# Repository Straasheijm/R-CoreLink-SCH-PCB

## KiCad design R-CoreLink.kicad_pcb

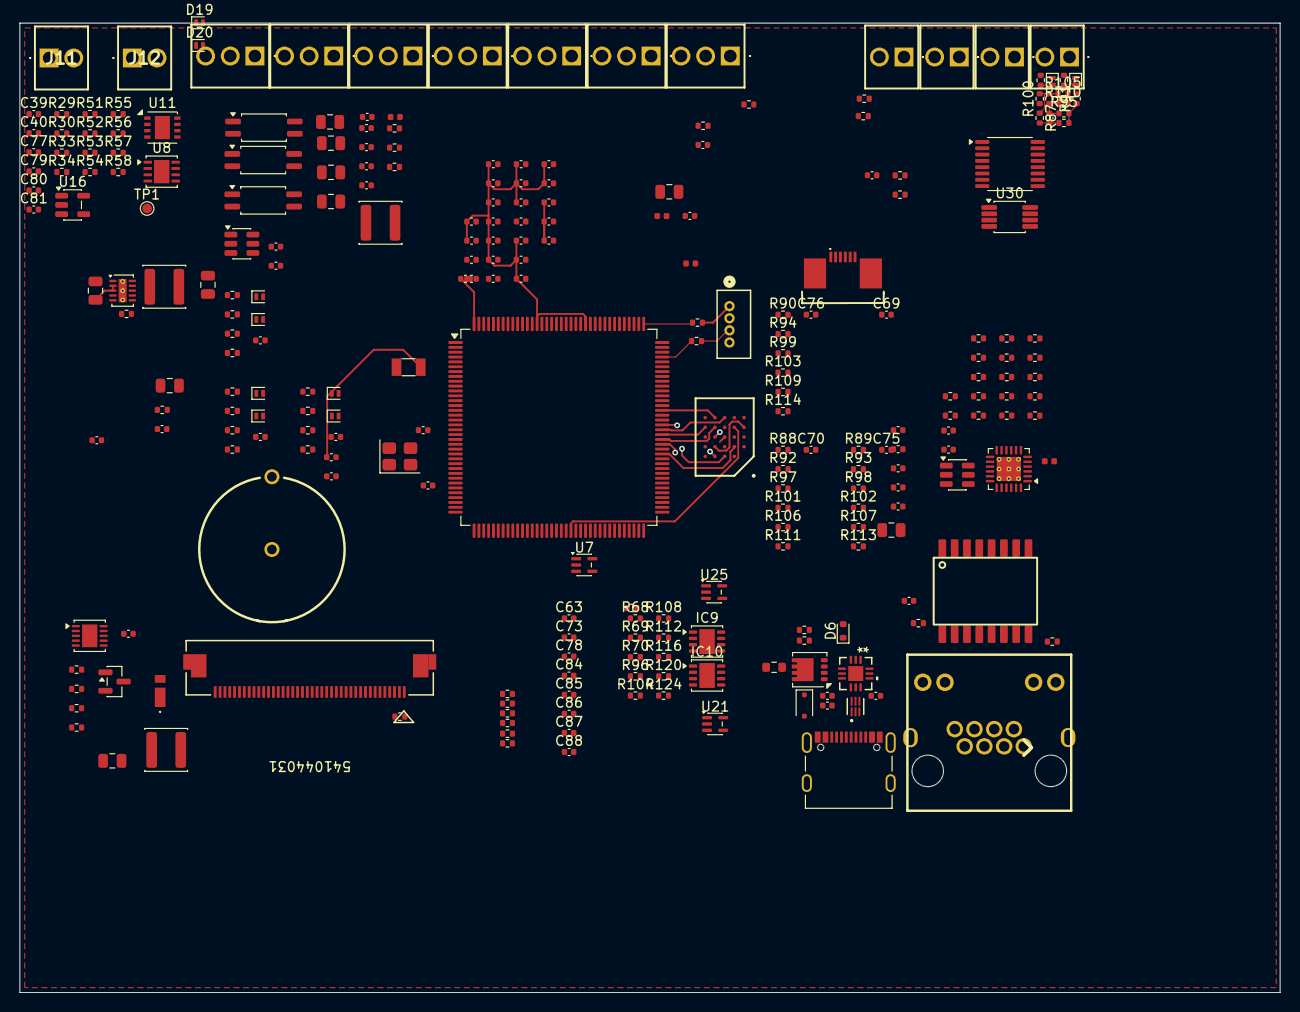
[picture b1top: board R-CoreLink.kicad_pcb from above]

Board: 4 copper layers, 130.0 x 100.0 mm, 260 parts (0 on the bottom side), 196 nets.

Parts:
BT1: Battery_Cell; CH23-1220LF
C1, C2, C4, C5, C7, C8, C9, C14, C15, C17, C18, C19, C20, C21, C22, C23, C24, C25, C32, C34, C36, C39, C40, C43, C47, C49, C51, C54, C56, C58, C63, C64, C65, C66, C67, C68, C71, C73, C74, C77, C78, C79, C80, C81, C83, C84, C85, C86, C87, C88: 100n; C_0402_1005Metric
C3: 1n; C_0402_1005Metric
C6, C10, C11, C26, C48, C50, C52, C53, C55, C62: 10u; C_0805_2012Metric
C12, C13, C41, C42: 15p; C_0402_1005Metric
C16, C28, C29: 4u7; C_0402_1005Metric
C27, C30, C31, C33, C35, C46, C57, C69, C70, C72, C75, C76: 1u; C_0402_1005Metric
C37, C38: 2u2; C_0402_1005Metric
C44, C45: 330p; C_0402_1005Metric
D2: ESD3Z24GW; D_SOD-323F
D6: RB530SM-40; D_SOD-523
D7: SDB160WS-AQ; SOD323HE
D11, D12, D13, D14, D15, D16, D17, D18, D19, D20: PESD3V3L1BSL; D_SOD-882
IC1: APS6408L-3OC-BA; BGA24C100P5X5_600X800X120
IC2: AL8866QFN-7; DFN-10-1EP_3x3mm_P0.5mm_EP1.58x2.35mm
IC9, IC10: MCP6n16-100E_MF; DFN-8-1EP_3x3mm_P0.65mm_EP1.6x2.56mm
J1: 541044031; CON_541044031_MOL
J2: RJHSE5384H1
J3, J5, J6, J7, J8, J9, J10: TBC05-03-1-G-G; TBC05031GG
J4: 10155435-00011LF; AMPHENOL_10155435-00011LF
J11, J12, J19, J20, J21, J22: TBC05-02-1-G-G; TBC05021GG
J13: 530470410; CONN04_530470410_MOL
J14: 1734839-6; 17348396
L1, L4, L7: MMZ1005A601ETD25; L_0402_1005Metric
L2, L3, L5: IFSC1515AHER100M01; L_Pulse_PA4332
Q1: DMG7430LFG; Diodes_PowerDI3333-8MOSFET
Q2: IRLML2060; SOT-23
R1, R9, R10, R11, R13, R21, R26, R36, R47, R51, R58, R70, R104, R112: 10K; R_0402_1005Metric
R2, R105, R106, R107, R109, R121, R122: 0; R_0402_1005Metric
R3, R4, R52, R53, R54, R55, R56, R57: 4K7; R_0402_1005Metric
R5, R6, R30, R37, R41, R44, R68, R69, R116, R120, R124: 100; R_0402_1005Metric
R7, R8: 75; R_0402_1005Metric
R12: 1K5; R_0402_1005Metric
R14, R16, R17, R18, R19, R20, R22, R23, R24, R28, R31, R32: 33; R_0402_1005Metric
R15, R25: 270; R_0402_1005Metric
R27: 330; R_0402_1005Metric
R29, R33, R34: 150; R_0402_1005Metric
R35: 2K4; R_0402_1005Metric
R38, R96, R108: 100K; R_0402_1005Metric
R39: 13K5; R_0402_1005Metric
R40: 47K; R_0402_1005Metric
R42: 12K1; R_0402_1005Metric
R45: 0; R_0603_1608Metric
R46: 250m; R_0402_1005Metric
R48: 270K; R_0402_1005Metric
R49: 10; R_0402_1005Metric
R71, R77, R81, R85, R95, R97, R98, R99, R100, R101, R102, R103: 5K; R_0402_1005Metric
R72, R78, R82, R86: 68; R_0402_1005Metric
R73, R74, R75, R76, R79, R80, R83, R84: 1K; R_0402_1005Metric
R87, R88, R89, R90, R110, R111, R113, R114: 22K; R_0402_1005Metric
R91, R92, R93, R94: 2K5; R_0402_1005Metric
STP1: STP1; L_0402_1005Metric
TH2: NTCG104BF473FT1X; R_0402_1005Metric
TP1: OP_OUT; TestPoint_Pad_D1.0mm
TR1: KMS-1102NL
U1: STM32H5E5ZJT6; LQFP-144_20x20mm_P0.5mm
U2: LAN8742A; VQFN-24-1EP_4x4mm_P0.5mm_EP2.5x2.5mm_ThermalVias
U3: USBLC6-4SC6; SOT-23-6
U4: TCPP01-M12; QFN12_TCPP01-M12_STM
U5: ECMF2-40A100N6; QFN6L_ECMF2_STM
U6: TPS62177DQC; WSON-10-1EP_2x3mm_P0.5mm_EP0.84x2.4mm_ThermalVias
U7: OPA333xxDCK; SOT-353_SC-70-5
U8: SN65HVD75DRBR; VSON-8-1EP_3x3mm_P0.65mm_EP1.6x2.4mm
U9: TPS561300DDCR; SOT-23-6
U11: NCV7344AMW3R2G; DFN-8-1EP_3x3mm_P0.65mm_EP1.55x2.4mm
U12, U13, U14: TCMT1100; SOP-4_4.4x2.6mm_P1.27mm
U15: TMUX1109PW; TSSOP-16_4.4x5mm_P0.65mm
U16: AP2171W; SOT-23-5
U21, U25: TLV9061xDCK; SOT-353_SC-70-5
U30: TMUX1121DGK; VSSOP-8_3x3mm_P0.65mm
Y1: XC32M4-24.000-F12NJDTL; Crystal_SMD_3225-4Pin_3.2x2.5mm
Y2: LFXTAL009678; Crystal_SMD_3215-2Pin_3.2x1.5mm

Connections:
+3.3V: C7.1, C11.1, C14.1, C15.1, C16.1, C17.1, C18.1, C19.1, C20.1, C21.1, C22.1, C23.1, C24.1, C25.1, C28.1, C29.1, C30.1, C31.1, C40.1, C57.1, C58.1, IC1.B4 (VDD), IC1.D1 (VDDQ_1), IC1.E4 (VDDQ_2), J1.4, J14.2, L1.1, L2.2, L4.2, R2.1, R3.1, R4.1, R9.1, R10.1, R11.1, R12.1, R13.1, R26.1, U1.17 (VDD), U1.30 (VDD), U1.39 (VDD), U1.52 (VDD), U1.62 (VDD), U1.72 (VDD), U1.84 (VDD), U1.94 (VDD), U1.106 (VDDSUSB), U1.108 (VDD), U1.121 (VDDIO2), U1.131 (VDD), U1.144 (VDD), U2.9 (VDDIO), U4.12 (VCC), U6.8 (~SLEEP), U6.10 (VOS), U8.8 (VCC), U11.5 (VIO)
+3.3VA: C32.1, C33.1, C34.1, C35.1, L4.1, U1.33 (VDDA)
+5V: C39.1, C52.1, C53.1, C81.1, L3.2, L7.1, R38.2, U11.3 (VDD), U16.5 (IN)
+5VA: C62.1, C63.1, C65.1, C78.1, C83.1, C84.1, C85.1, C86.1, C87.1, C88.1, IC9.1 (EN), IC9.8 (VDD), IC10.1 (EN), IC10.8 (VDD), L7.2, R91.2, R92.2, R93.2, R94.2, U7.5 (V+), U15.13 (VDD), U21.5 (V+), U25.5 (V+), U30.8 (V_{DD})
+VDC: C10.1, C26.1, C48.1, C50.1, C51.1, C55.1, C74.1, IC2.1 (VIN), L5.2, Q1.S, R45.2, R49.1, U4.4 (SOURCE), U6.2 (VIN), U6.3 (EN), U9.3 (VIN)
/ETH/LED_G: J2.12, U2.2 (LED2/~INTSEL)
/ETH/LED_Y: J2.10, U2.3 (LED1/REGOFF)
/MCU/B0: J1.21, U1.111 (PC10)
/MCU/B2: J1.23, U1.119 (PD5)
/MCU/B3: J1.24, U1.42 (PA6)
/MCU/B4: J1.25, U1.117 (PD3)
/MCU/B5: J1.26, U1.124 (PG9)
/MCU/B6: J1.27, U1.53 (PF13)
/MCU/B7: J1.28, U1.55 (PF15)
/MCU/CLK: J1.30, U1.86 (PD15)
/MCU/DE: J1.34, U1.18 (PF6)
/MCU/G0: J1.13, U1.76 (PB15)
/MCU/G1: J1.14, U1.2 (PE3)
/MCU/G2: J1.15, U1.27 (PC1)
/MCU/G3: J1.16, U1.19 (PF7)
/MCU/G4: J1.17, U1.69 (PB10)
/MCU/G5: J1.18, U1.54 (PF14)
/MCU/G6: J1.19, U1.22 (PF10)
/MCU/G7: J1.20, U1.116 (PD2)
/MCU/HSYNC: J1.32, U1.28 (PC2)
/MCU/R0: J1.5, U1.68 (PE15)
/MCU/R1: J1.6, U1.73 (PB12)
/MCU/R2: J1.7, U1.5 (PE6)
/MCU/R3: J1.8, U1.123 (PD7)
/MCU/R4: J1.9, U1.78 (PD9)
/MCU/R5: J1.10, U1.77 (PD8)
/MCU/R6: J1.11, U1.80 (PD11)
/MCU/R7: J1.12, U1.20 (PF8)
/MCU/SRAM_CLK: IC1.B2 (CLK), U1.85 (PD14)
/MCU/SRAM_DQS: IC1.C3 (DQS/_DM), U1.15 (PF5)
/MCU/SRAM_IO0: IC1.D3 (ADQ0), U1.56 (PG0)
/MCU/SRAM_IO1: IC1.D2 (ADQ1), U1.57 (PG1)
/MCU/SRAM_IO2: IC1.C4 (ADQ2), U1.87 (PG2)
/MCU/SRAM_IO3: IC1.D4 (ADQ3), U1.88 (PG3)
/MCU/SRAM_IO4: IC1.D5 (ADQ4), U1.89 (PG4)
/MCU/SRAM_IO5: IC1.E3 (ADQ5), U1.90 (PG5)
/MCU/SRAM_IO6: IC1.E2 (ADQ6), U1.110 (PA15)
/MCU/SRAM_IO7: IC1.E1 (ADQ7), U1.113 (PC12)
/MCU/SRAM_NCS: IC1.A3 (CE#), U1.91 (PG6)
/MCU/TOUCH_INT: J14.4, U1.135 (PB5)
/MCU/TOUCH_RESET: J14.1, U1.139 (PB8)
/MCU/T_SCL: J14.6, R3.2, U1.136 (PB6)
/MCU/T_SDA: J14.5, R4.2, U1.137 (PB7)
/MCU/VBAT: BT1.1 (+), C27.1, C56.1, R2.2, U1.6 (VBAT)
/MCU/VCAP: C36.1, C37.1, C38.1, U1.70 (VCAP), U1.95 (VDD11USB), U1.142 (VCAP)
/MCU/VSYNC: J1.33, U1.29 (PC3)
/MCU/XL: R37.1, U1.14 (PF4)
/MCU/XR: R5.1, U1.34 (PA0)
/MCU/YD: R6.1, U1.13 (PF3)
/MCU/YU: R44.1, U1.26 (PC0)
/MUX_frontend/AnalogBackend/OUT_100x: IC10.7 (VOUT), R53.1, R70.2
/MUX_frontend/AnalogBackend/OUT_H: R52.1, U25.1 (+), U25.4
/MUX_frontend/AnalogBackend/OUT_L: R54.1, U21.1 (+), U21.4
/MUX_frontend/MUX_AN_IN/AnalogInput1/Out_L: C66.2, R78.2, R97.1, R111.1, U15.12 (S2B)
/MUX_frontend/MUX_AN_IN/AnalogInput2/Out_H: C67.1, D15.2 (A2), R79.2, R81.1, R89.2, U15.6 (SA3)
/MUX_frontend/MUX_AN_IN/AnalogInput2/Out_L: C67.2, R82.2, R98.1, R113.1, U15.11 (S3B)
/MUX_frontend/MUX_AN_IN/AnalogInput3/Out_H: C68.1, D17.2 (A2), R83.2, R85.1, R90.2, U15.7 (SA4)
/MUX_frontend/MUX_AN_IN/AnalogInput3/Out_L: C68.2, R86.2, R99.1, R114.1, U15.10 (S4B)
/MUX_frontend/MUX_AN_IN/AnalogInput/Out_H: C64.1, D11.2 (A2), R71.1, R73.2, R87.2, R121.1, U15.4 (SA1)
/MUX_frontend/MUX_AN_IN/AnalogInput/Out_L: C64.2, C66.1, D13.2 (A2), R72.2, R75.2, R77.1, R88.2, R95.1, R110.1, R122.1, U15.5 (SA2)
/MUX_frontend/MUX_AN_IN/IN0_H: J19.1, R73.1
/MUX_frontend/MUX_AN_IN/IN0_L: J19.2, R74.1
/MUX_frontend/MUX_AN_IN/IN1_H: J20.1, R75.1
/MUX_frontend/MUX_AN_IN/IN1_L: J20.2, R76.1
/MUX_frontend/MUX_AN_IN/IN2_H: J21.1, R79.1
/MUX_frontend/MUX_AN_IN/IN2_L: J21.2, R80.1
/MUX_frontend/MUX_AN_IN/IN3_H: J22.1, R83.1
/MUX_frontend/MUX_AN_IN/IN3_L: J22.2, R84.1
/MUX_frontend/MUX_AN_IN/MUX_O_H: IC10.3 (VIP), R121.2, U15.8 (DA), U25.3 (-), U30.2, U30.6
/MUX_frontend/MUX_AN_IN/MUX_O_L: IC10.2 (VIM), R122.2, U15.9 (DB), U21.3 (-)
/USB/CC1c: C44.1, D20.2 (A2), J4.A5 (CC1), R58.2, U4.7 (CC1c)
/USB/CC2c: C45.1, D19.2 (A2), J4.B5 (CC2), R51.2, U4.9 (CC2c)
AN_OUT_100: C79.1, R53.2, R56.2, U1.63 (PE10)
AN_OUT_H: C77.1, R52.2, R55.2, U1.64 (PE11)
AN_OUT_L: C80.1, R54.2, R57.2, U1.65 (PE12)
DAC: R68.1, R69.2, U1.41 (PA5)
FDCAN_RX: U1.103 (PA11), U11.4 (RXD)
FDCAN_TX: U1.104 (PA12), U11.1 (TXD)
GND: BT1.2 (-), C1.2, C2.2, C4.2, C5.2, C6.2, C7.2, C8.1, C9.1, C10.2, C11.2, C12.2, C13.2, C14.2, C15.2, C16.2, C17.2, C18.2, C19.2, C20.2, C21.2, C22.2, C23.2, C24.2, C25.2, C27.2, C28.2, C29.2, C30.2, C31.2, C36.2, C37.2, C38.2, C39.2, C40.2, C41.2, C42.2, C43.2, C44.2, C45.2, C46.2, C47.2, C48.2, C50.2, C51.2, C52.2, C53.2, C54.2, C55.2, C56.2, C57.2, C58.2, C72.2, C74.2, C81.2, D2.2 (A), D19.1 (A1), D20.1 (A1), IC1.B3 (VSS), IC1.C1 (VSSQ_1), IC1.E5 (VSSQ_2), IC2.5 (AGND), IC2.9 (PGND), IC2.11 (EP), J1.3, J1.29, J1.36, J1.P1, J1.P2, J4.A1_B12 (GND), J4.B1_A12 (GND__1), J4.SH1 (SHIELD), J4.SH2 (SHIELD__1), J4.SH3 (SHIELD__2), J4.SH4 (SHIELD__3), J13.2, J14.3, J14.MP1, J14.MP2, R1.2, R15.1, R21.2, R25.1, R35.1, R39.1, R42.2, R46.1, R47.2, STP1.1, U1.16 (VSS), U1.38 (VSS), U1.51 (VSS), U1.61 (VSS), U1.71 (VSS), U1.83 (VSS), U1.93 (VSS), U1.98 (VSSUSB), U1.107 (VSS), U1.120 (VSS), U1.130 (VSS), U1.143 (VSS), U2.25 (VSS), U3.2 (GND), U4.2 (GND), U4.13 (GND), U5.3 (GND), U5.4 (GND), U6.1 (PGND), U6.4 (NC), U6.5 (FB), U6.6 (AGND), U6.11 (PAD), U8.5 (GND), U9.1 (GND), U11.2 (VSS), U11.8 (STBY), U11.9 (VSS), U16.2 (GND), Y1.2 (G), Y1.4 (G)
GNDA: C32.2, C33.2, C34.2, C35.2, C62.2, C63.2, C65.2, C69.2, C70.2, C71.2, C75.2, C76.2, C77.2, C78.2, C79.2, C80.2, C83.2, C84.2, C85.2, C86.2, C87.2, C88.2, D11.1 (A1), D12.1 (A1), D13.1 (A1), D14.1 (A1), D15.1 (A1), D16.1 (A1), D17.1 (A1), D18.1 (A1), IC9.4 (VSS), IC10.4 (VSS), R40.1, R55.1, R56.1, R100.1, R101.1, R102.1, R103.1, R116.1, R120.1, R124.1, STP1.2, U1.31 (VSSA), U7.2 (V-), U15.3 (VSS), U15.15 (GND), U21.2 (V-), U25.2 (V-), U30.4 (GND)
LED+: C26.2, D7.1 (K), J1.2, R48.1
LED-: IC2.2 (CSP), J1.1, R49.2
LED_DIM: IC2.6 (DIM), R41.2
MDC: R20.1, U1.21 (PF9)
MDIO: R16.1, U1.134 (PB4)
NRST: IC1.A4 (RST#), J13.4, R27.1, U1.25 (NRST), U2.15 (~RST)
NTC: C71.1, R40.2, TH2.2, U1.48 (PB2)
unnamed: C3.1, R7.2, R8.2
unnamed: C3.2, J2.SH
unnamed: C69.1, R71.2, R91.1, R95.2
unnamed: C70.1, R77.2, R92.1, R97.2
unnamed: C73.2, R96.1
unnamed: C75.1, R81.2, R93.1, R98.2
unnamed: C76.1, R85.2, R94.1, R99.2
unnamed: D2.1 (K), D6.2 (A), J4.A4_B9 (VBUS), J4.B4_A9 (VBUS__1), Q1.D, R36.1, R45.1, U16.1 (OUT)
unnamed: C43.1, D6.1 (K), U4.8 (IN_GD)
unnamed: D7.2 (A), L5.1, Q2.3 (D)
unnamed: D12.2 (A2), R74.2, R105.2, R110.2
unnamed: D14.2 (A2), R76.2, R106.2, R111.2
unnamed: D16.2 (A2), R80.2, R107.2, R113.2
unnamed: D18.2 (A2), R84.2, R109.2, R114.2
unnamed: C72.1, IC2.7 (COMP)
unnamed: IC2.8 (CS), Q2.2 (S), R46.2
unnamed: IC2.10 (DRV), Q2.1 (G)
unnamed: IC2.3 (OVP), R47.1, R48.2
unnamed: IC9.6 (VFG), R112.1, R116.2
unnamed: IC9.2 (VIM), R104.1, U30.1
unnamed: IC9.3 (VIP), R96.2, R104.2, U7.4
unnamed: IC9.7 (VOUT), R108.2, R112.2
unnamed: IC9.5 (VREF), R120.2
unnamed: IC10.6 (VFG), R68.2, R70.1
unnamed: IC10.5 (VREF), R69.1
unnamed: J1.37, R5.2
unnamed: J1.38, R6.2
unnamed: J1.39, R37.2
unnamed: J1.40, R44.2
unnamed: J2.4, J2.5
unnamed: J2.7, J2.8
unnamed: J2.9, R15.2
unnamed: J2.11, R25.2
unnamed: J4.A7 (DN1), J4.B7 (DN2), U5.2 (D-)
unnamed: J4.A6 (DP1), J4.B6 (DP2), U5.1 (D+)
unnamed: J13.1, R31.2
unnamed: J13.3, R32.2
unnamed: R72.1, R87.1, R100.2, R105.1
unnamed: R78.1, R88.1, R101.2, R106.1
unnamed: R82.1, R89.1, R102.2, R107.1
unnamed: R86.1, R90.1, R103.2, R109.1
unnamed: R124.2, U30.5
unnamed: R7.1, TR1.10 (CT_RX_CABLE)
unnamed: C1.1, C2.1, C4.1, C5.1, C6.1, L1.2, TR1.2 (CT_TX_PHY), TR1.7 (CT_RX_PHY), U2.1 (VDD2A), U2.19 (VDD1A), U3.5 (VBUS)
unnamed: R8.1, TR1.15 (CT_TX_CABLE)
unnamed: TR1.6 (RD+), U2.23 (RXP), U3.1 (I/O1)
unnamed: TR1.8 (RD-), U2.22 (RXN), U3.6 (I/O4)
unnamed: J2.3, TR1.11 (RX+)
unnamed: J2.6, TR1.9 (RX-)
unnamed: TR1.1 (TD+), U2.21 (TXP), U3.4 (I/O3)
unnamed: TR1.3 (TD-), U2.20 (TXN), U3.3 (I/O2)
unnamed: J2.1, TR1.16 (TX+)
unnamed: J2.2, TR1.14 (TX-)
unnamed: R32.1, U1.105 (PA13)
unnamed: R31.1, U1.109 (PA14)
unnamed: TP1.1 (1_1), U1.47 (PB1)
unnamed: C41.1, U1.8 (PC14-OSC32_IN), Y2.1
unnamed: C42.1, U1.9 (PC15-OSC32_OUT), Y2.2
unnamed: R41.1, U1.125 (PG10)
unnamed: C12.1, U1.23 (PH0-OSC_IN), Y1.1
unnamed: C13.1, U1.24 (PH1-OSC_OUT), Y1.3
unnamed: R1.1, U1.138 (BOOT0)
unnamed: R9.2, R28.2, U2.11 (CRS_DV/MODE2)
unnamed: R20.2, U2.13 (MDC)
unnamed: R12.2, R16.2, U2.12 (MDIO)
unnamed: R42.1, U2.24 (RBIAS)
unnamed: R10.2, R14.2, U2.8 (RXD0/MODE0)
unnamed: R11.2, R22.2, U2.7 (RXD1/MODE1)
unnamed: R21.1, U2.10 (RXER/PHYAD0)
unnamed: R24.2, U2.17 (TXD0)
unnamed: R23.2, U2.18 (TXD1)
unnamed: R18.2, U2.16 (TXEN)
unnamed: C8.2, C9.2, U2.6 (VDDCR)
unnamed: R19.2, U2.5 (XTAL1/CLKIN)
unnamed: R13.2, R17.2, U2.14 (~INT/REFCLKO)
unnamed: Q1.G, U4.5 (GATE)
unnamed: R35.2, R36.2, U4.6 (VBUS_CTRL)
unnamed: R27.2, U6.7 (PG)
unnamed: L2.1, U6.9 (SW)
unnamed: C73.1, R108.1, U7.1 (+)
unnamed: J11.2, R30.2, U8.6 (A)
unnamed: J11.1, R30.1, U8.7 (B)
unnamed: R33.2, U8.2 (~RE), U8.3 (DE)
unnamed: R34.2, U8.1 (R)
unnamed: C49.1, L3.1, U9.2 (SW)
unnamed: C49.2, U9.6 (VBST)
unnamed: C54.1, R38.1, R39.2, U9.4 (VFB)
unnamed: J12.1, R29.1, U11.7 (CANH)
unnamed: J12.2, R29.2, U11.6 (CANL)
RCC_MCO_ETH: R19.1, U1.100 (PA8)
RMII_REF_CLK: R17.1, U1.35 (PA1)
RMII_RXD0: R14.1, U1.3 (PE4)
RMII_RXD1: R22.1, U1.4 (PE5)
RMII_TXD0: R24.1, U1.128 (PG13)
RMII_TXD1: R23.1, U1.127 (PG12)
RMII_TX_EN: R18.1, U1.126 (PG11)
SER_RX: R34.1, U1.58 (PE7)
SER_TX: U1.59 (PE8), U8.4 (D)
UCPD.CC1: R58.1, U4.3 (CC1)
UCPD.CC2: R51.1, U4.1 (CC2)
UCPD.FLT: R26.2, U4.11 (FLT/)
USB_HS_N: U1.96 (OTG_HS_DM), U5.5 (D-_TO_IC)
USB_HS_P: U1.97 (OTG_HS_DP), U5.6 (D+_TO_IC)
VREF+: C46.1, C47.1, TH2.1, U1.32 (VREF+)
